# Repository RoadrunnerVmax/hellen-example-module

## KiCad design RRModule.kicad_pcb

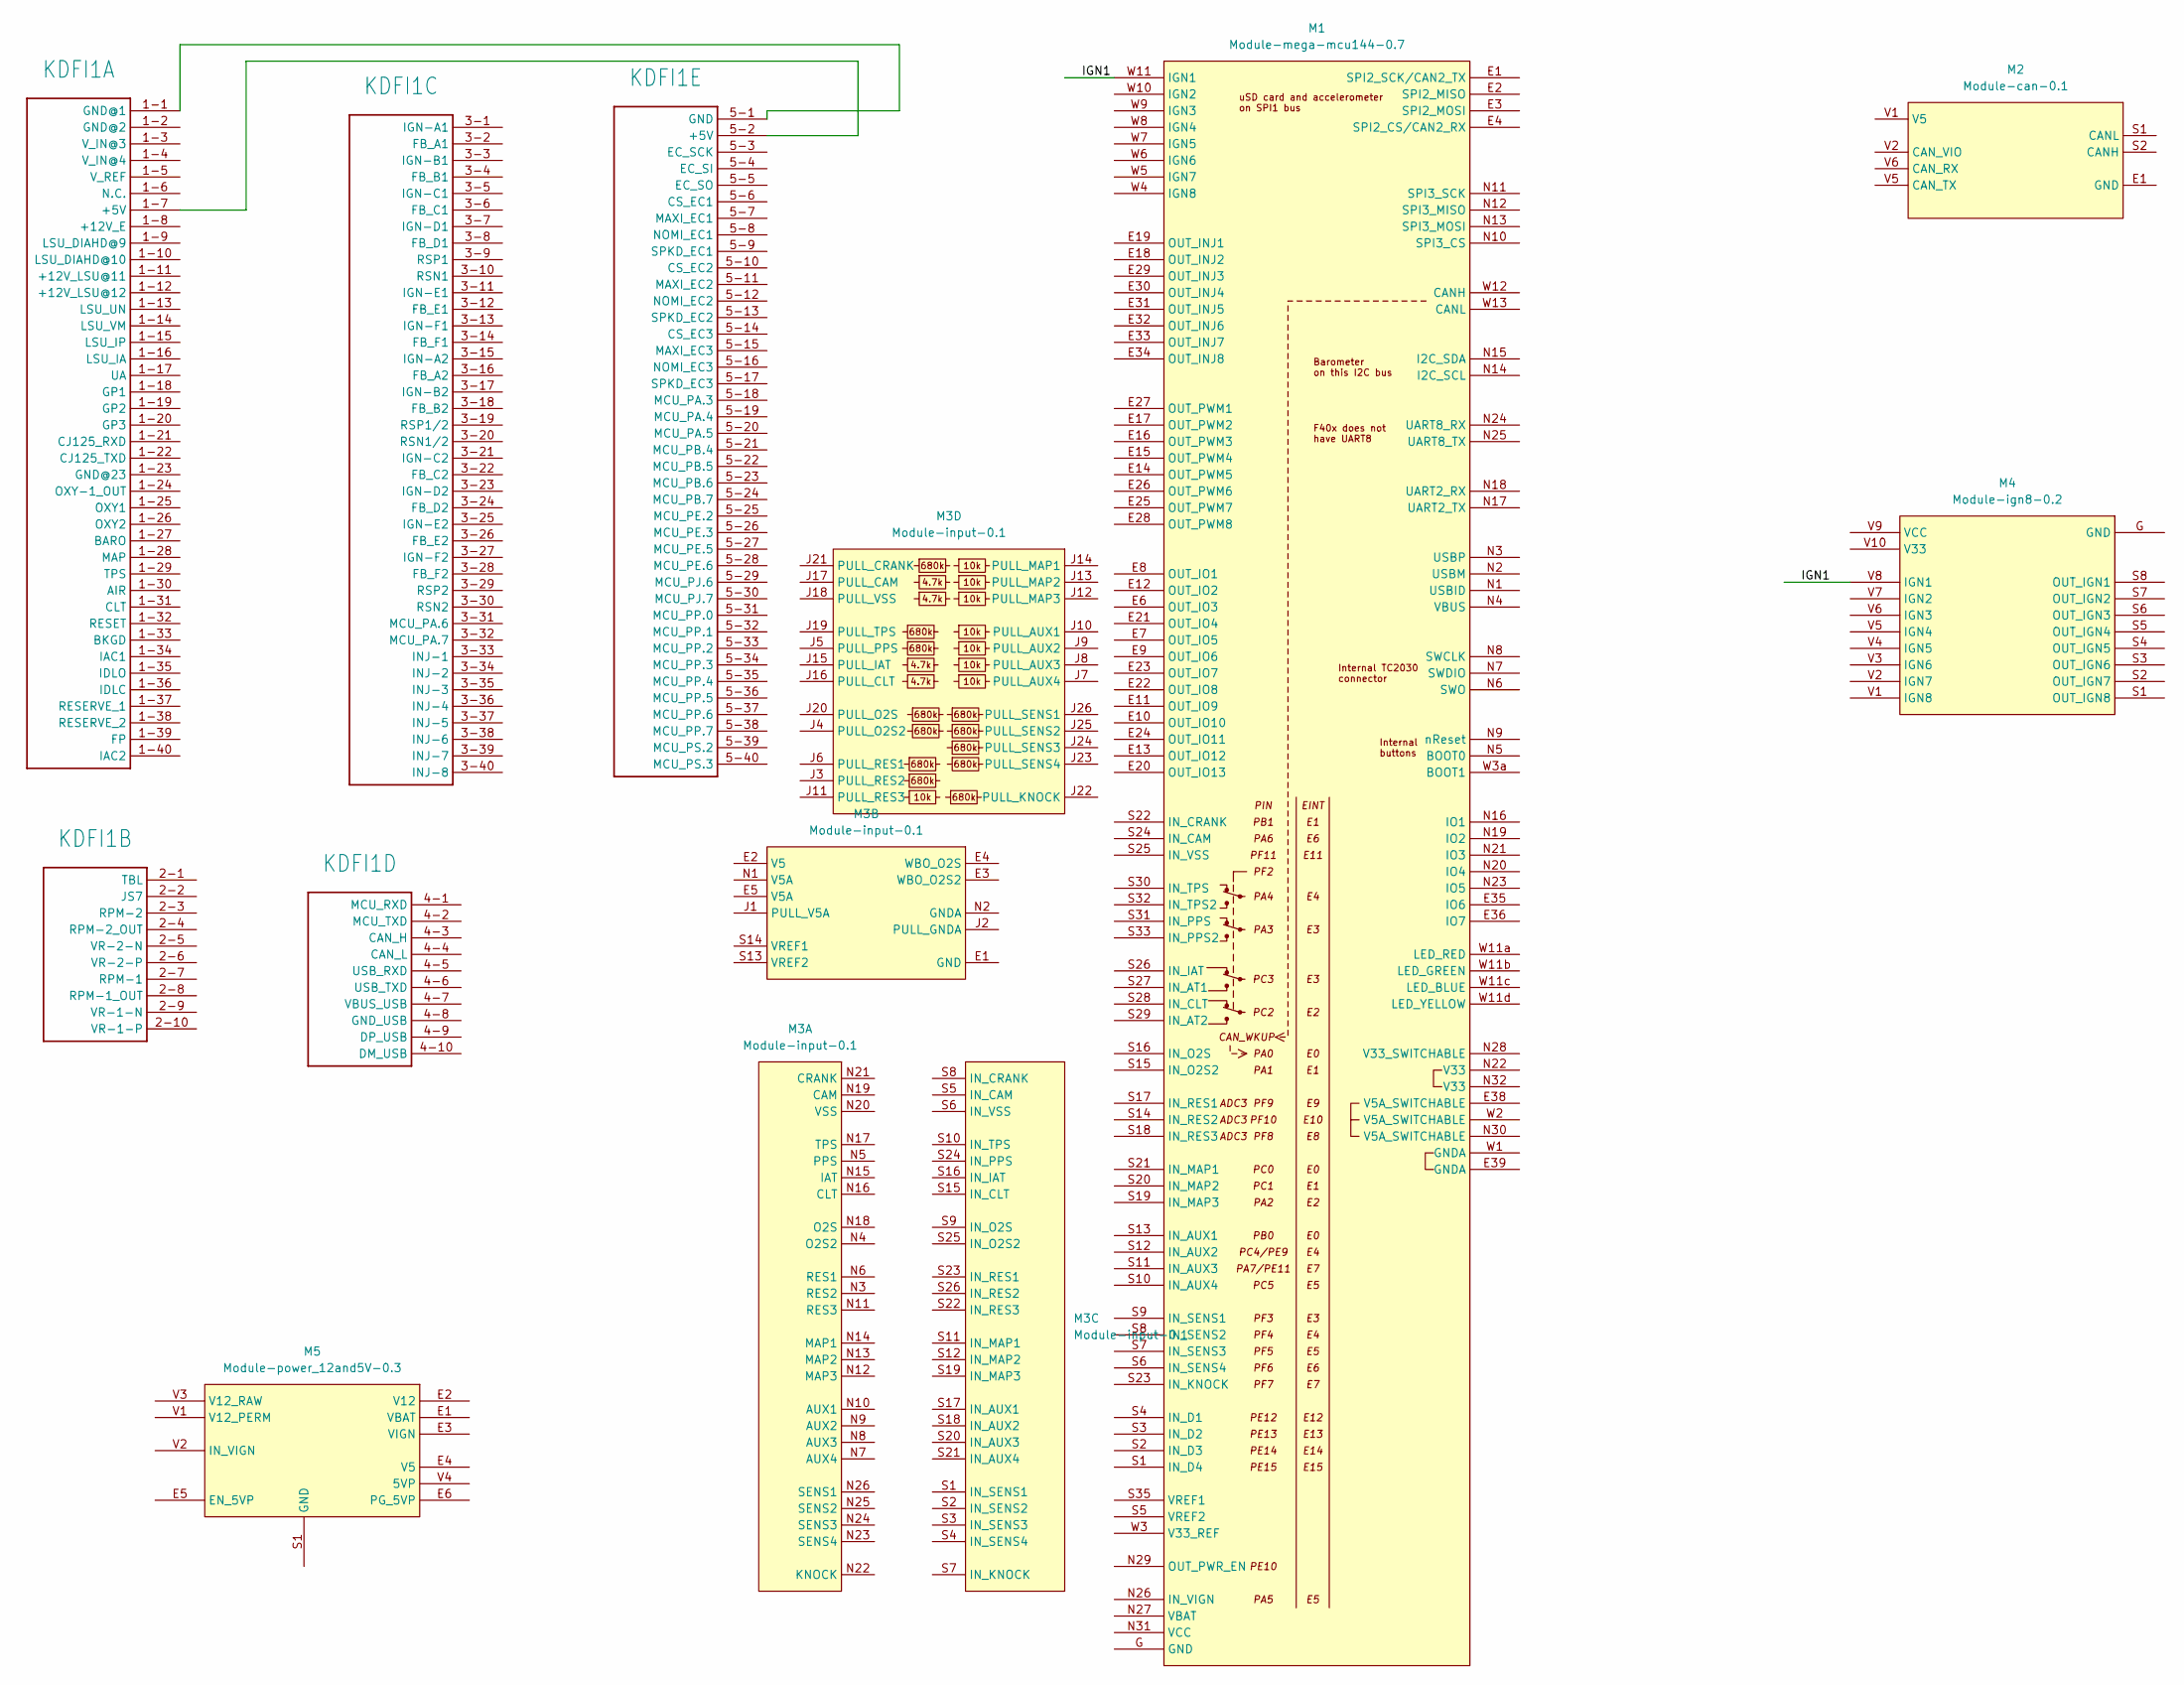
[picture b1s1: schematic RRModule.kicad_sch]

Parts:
KDFI1: KDFI_V1.4_MODULE
M1: Module-mega-mcu144-0.7; mega-mcu144
M2: Module-can-0.1; can
M3: Module-input-0.1; input
M4: Module-ign8-0.2; ign8
M5: Module-power_12and5V-0.3; power_12and5V

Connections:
/IGN1: M1.W11 (IGN1), M4.V8 (IGN1)
unnamed: KDFI1.1-7 (+5V), KDFI1.5-2 (+5V)
unnamed: KDFI1.1-1 (GND@1), KDFI1.5-1 (GND)

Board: 2 copper layers, 6 parts (0 on the bottom side), 3 nets, no tracks yet.
